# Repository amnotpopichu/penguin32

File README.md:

# penguin32
Penguin32 is a esp32 devboard developed on the esp32 s3fn8 board but with a big penguin on it. why penguin? why not? the main goal here was to develop and learn bare chip work

# Firmware + CAD
N/A, all the necessary programs are preflashed onto the s3 chip. Also no cad for obvious reasons, its just a devboard

# Images
Not sure why some of the models dont actaully render, and some are upside down, so forgive the pcb looking kinda odd.

# Notes
flash not needed thanks to the onboard flash. this is my first time doing bare chip development so im pretty happy with how it turned out given i did it in about 3 days to attempt to qualify for outpost. Honestly i can't believe some of the stuff (routing) took me so long, but i guess i finished at the end of the day so its fine. Also i have two seperate BOMs, a regular BOM, and then a BOM for specific pick and place components. Also i had to use 5 pcba instead of 2, because otherwise it would have made do standard pcba -- which is more expenisve. gsdl doesnt work because jlc doesn't allow it over a certain price.

| Line Item              | Amount (USD) |
|------------------------|--------------|
| MERCHANDISE TOTAL      | 65.78        |
| SHIPPING CHARGE        | 42.78        |
| Customs duties & taxes | 17.78        |
| DISCOUNT               | -15.00       |
| SALES TAX              | 4.90         |
| ORDER TOTAL            | 116.24       |

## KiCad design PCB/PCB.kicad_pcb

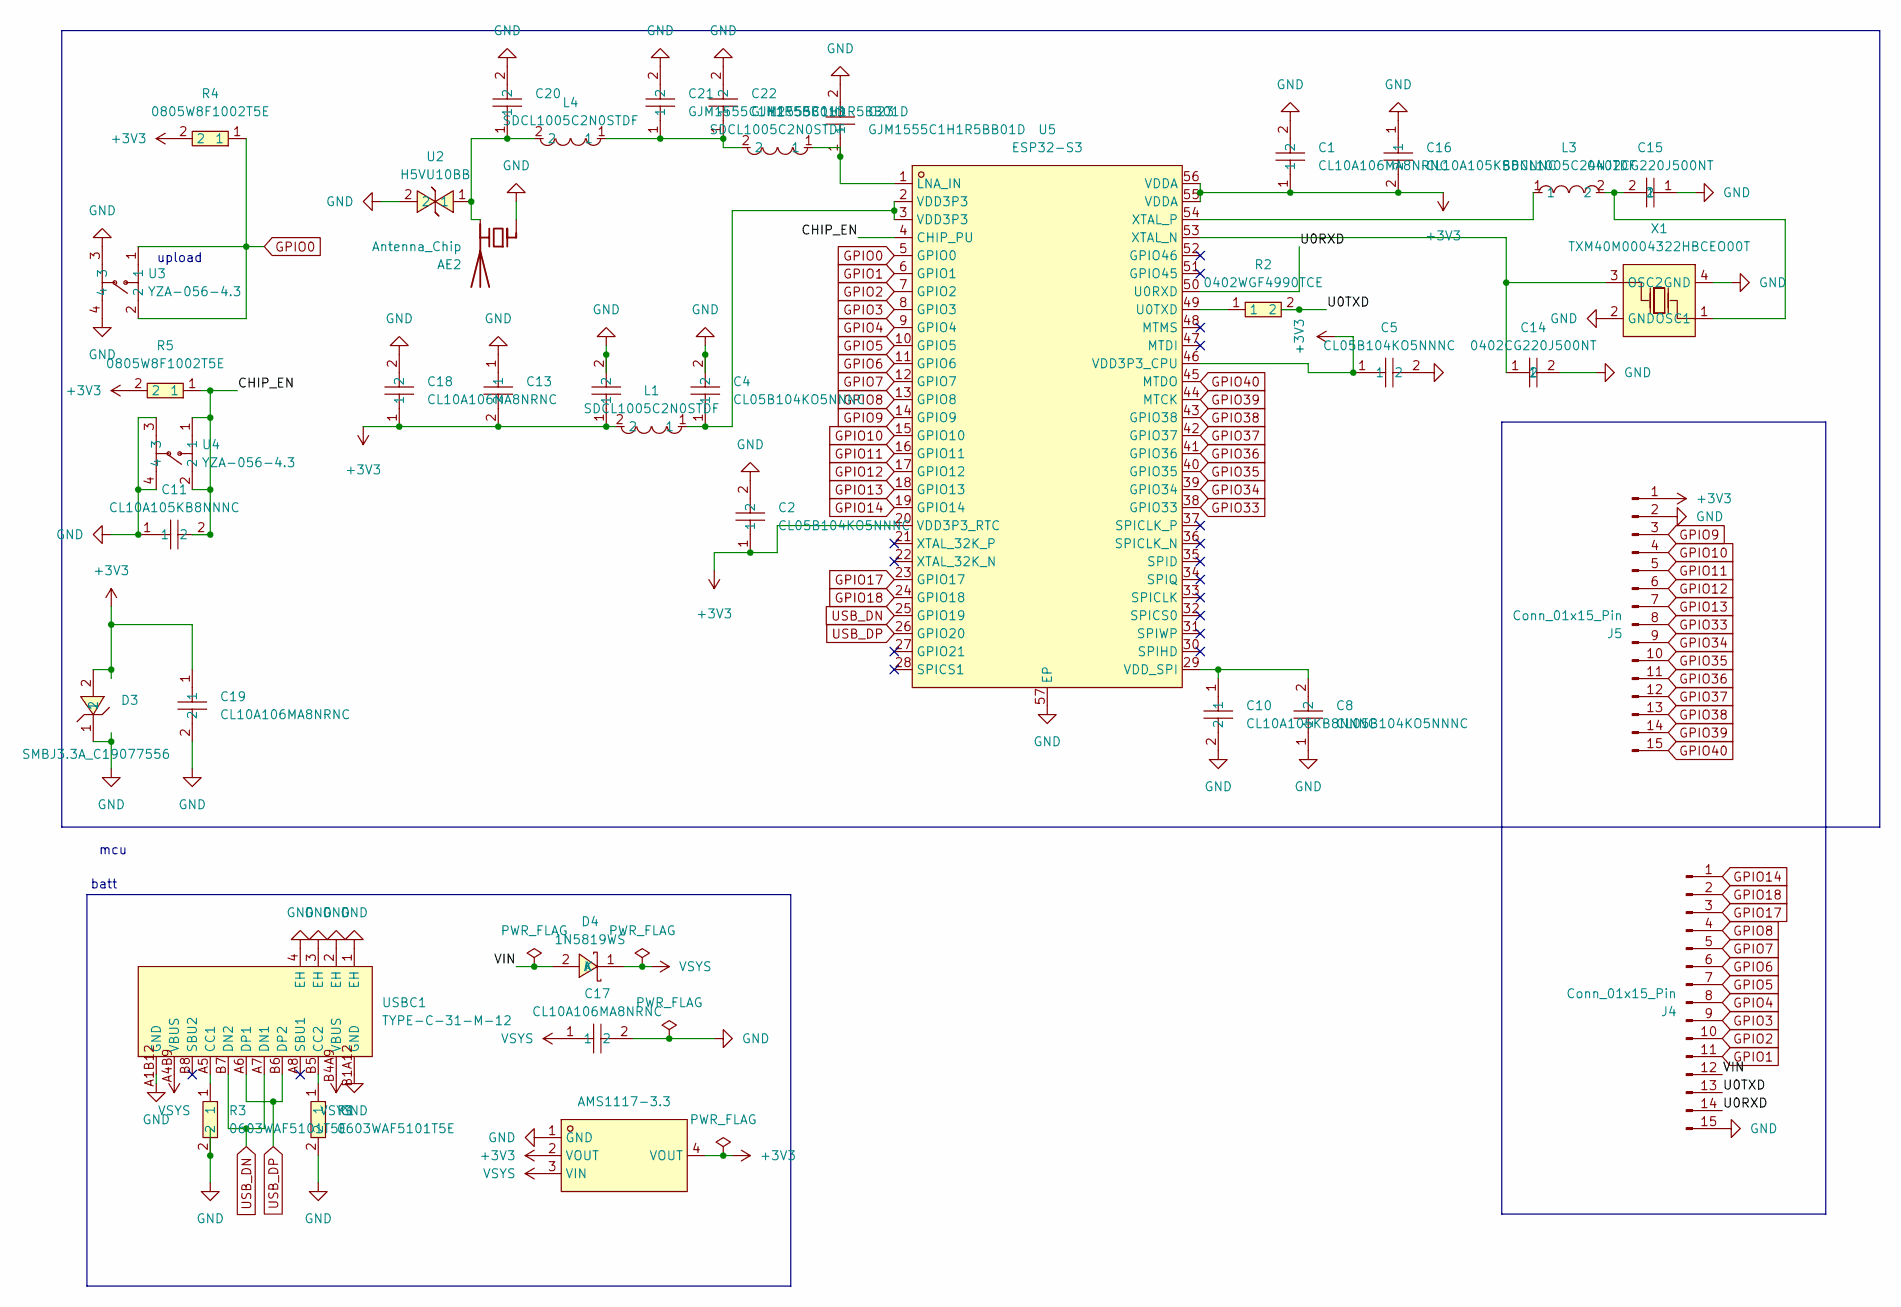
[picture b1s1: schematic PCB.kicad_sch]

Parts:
AE2: Antenna_Chip; ESPRESSIF_ESP32_MIFA_2.4GHz_Right
C1, C17, C18, C19: CL10A106MA8NRNC; C0603; MPN CL10A106MA8NRNC; LCSC Part C96446
C2, C3, C4, C5, C8: CL05B104KO5NNNC; C0402; MPN CL05B104KO5NNNC; LCSC Part C1525
C10, C11, C13, C16: CL10A105KB8NNNC; C0603; MPN CL10A105KB8NNNC; LCSC Part C15849
C14, C15: 0402CG220J500NT; C0402; MPN 0402CG220J500NT; LCSC Part C1555
C20, C21, C22, C23: GJM1555C1H1R5BB01D; C0402; MPN GJM1555C1H1R5BB01D; LCSC Part C76900
D3: SMBJ3.3A_C19077556; SMB_L4.6-W3.6-LS5.3-RD; MPN SMBJ3.3A; LCSC Part C19077556
D4: 1N5819WS; SOD-323_L1.8-W1.3-LS2.5-RD; MPN 1N5819WS; LCSC Part C191023
J4, J5: Conn_01x15_Pin; PinHeader_1x15_P2.54mm_Vertical
L1, L2, L4: SDCL1005C2N0STDF; L0402; MPN SDCL1005C2N0STDF; LCSC Part C43365
L3: SDCL1005C24NJTDF; L0402-RD; MPN SDCL1005C24NJTDF; LCSC Part C74301
R1, R3: 0603WAF5101T5E; R0603; MPN 0603WAF5101T5E; LCSC Part C23186
R2: 0402WGF4990TCE; R0402; MPN 0402WGF4990TCE; LCSC Part C4125
R4, R5: 0805W8F1002T5E; R0805; MPN 0805W8F1002T5E; LCSC Part C17414
U1: AMS1117-3.3; SOT-223-3_L6.5-W3.4-P2.30-LS7.0-BR; MPN AMS1117-3.3; LCSC Part C6186
U2: H5VU10BB; DFN1006-2L-BI; MPN H5VU10BB; LCSC Part C20615786
U3, U4: YZA-056-4.3; SW-SMD_4P-L4.5-W4.5-P3.00-LS6.8; MPN YZA-056-4.3; LCSC Part C49108646
U5: ESP32-S3; QFN-56_L7.0-W7.0-P0.40-TL-EP4.0; MPN ESP32-S3FN8; LCSC Part C2913196
USBC1: TYPE-C-31-M-12; USB-C_SMD-TYPE-C-31-M-12_1; MPN TYPE-C-31-M-12; LCSC Part C165948
X1: TXM40M0004322HBCEO00T; CRYSTAL-SMD_4P-L3.2-W2.5-BL-2; MPN TXM40M0004322HBCEO00T; LCSC Part C284179

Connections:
+3V3: C1.1, C2.1, C3.1, C5.1, C13.2, C16.2, C18.1, C19.1, D3.2, J5.1, L1.2, R4.2, R5.2, U1.2 (VOUT), U1.4 (VOUT), U5.20 (VDD3P3_RTC), U5.46 (VDD3P3_CPU), U5.55 (VDDA), U5.56 (VDDA)
/CHIP_EN: C11.2, R5.1, U4.1, U4.2, U5.4 (CHIP_PU)
/U0RXD: J4.14, U5.50 (U0RXD)
/U0TXD: J4.13, R2.2
/VIN: D4.2 (A), J4.12
GND: AE2.1 (FEED), C1.2, C2.2, C3.2, C4.2, C5.2, C8.1, C10.2, C11.1, C13.1, C14.2, C15.1, C16.1, C17.2, C18.2, C19.2, C20.2, C21.2, C22.2, C23.2, D3.1, J4.15, J5.2, R1.2, R3.2, U1.1 (GND), U2.2, U3.3, U3.4, U4.3, U4.4, U5.57 (EP), USBC1.1 (EH), USBC1.2 (EH), USBC1.3 (EH), USBC1.4 (EH), USBC1.A1B12 (GND), USBC1.B1A12 (GND), X1.2 (GND), X1.4 (GND)
GPIO0: R4.1, U3.1, U3.2, U5.5 (GPIO0)
GPIO1: J4.11, U5.6 (GPIO1)
GPIO2: J4.10, U5.7 (GPIO2)
GPIO3: J4.9, U5.8 (GPIO3)
GPIO4: J4.8, U5.9 (GPIO4)
GPIO5: J4.7, U5.10 (GPIO5)
GPIO6: J4.6, U5.11 (GPIO6)
GPIO7: J4.5, U5.12 (GPIO7)
GPIO8: J4.4, U5.13 (GPIO8)
GPIO9: J5.3, U5.14 (GPIO9)
GPIO10: J5.4, U5.15 (GPIO10)
GPIO11: J5.5, U5.16 (GPIO11)
GPIO12: J5.6, U5.17 (GPIO12)
GPIO13: J5.7, U5.18 (GPIO13)
GPIO14: J4.1, U5.19 (GPIO14)
GPIO17: J4.3, U5.23 (GPIO17)
GPIO18: J4.2, U5.24 (GPIO18)
GPIO33: J5.8, U5.38 (GPIO33)
GPIO34: J5.9, U5.39 (GPIO34)
GPIO35: J5.10, U5.40 (GPIO35)
GPIO36: J5.11, U5.41 (GPIO36)
GPIO37: J5.12, U5.42 (GPIO37)
GPIO38: J5.13, U5.43 (GPIO38)
GPIO39: J5.14, U5.44 (MTCK)
GPIO40: J5.15, U5.45 (MTDO)
unnamed: AE2.2 (PCB_Trace), C20.1, L4.2, U2.1
unnamed: C4.1, L1.1, U5.2 (VDD3P3), U5.3 (VDD3P3)
unnamed: C21.1, C22.1, L2.2, L4.1
unnamed: C23.1, L2.1, U5.1 (LNA_IN)
unnamed: R2.1, U5.49 (U0TXD)
unnamed: C8.2, C10.1, U5.29 (VDD_SPI)
unnamed: C14.1, U5.53 (XTAL_N), X1.3 (OSC2)
unnamed: L3.1, U5.54 (XTAL_P)
unnamed: R3.1, USBC1.A5 (CC1)
unnamed: R1.1, USBC1.B5 (CC2)
unnamed: C15.2, L3.2, X1.1 (OSC1)
USB_DN: U5.25 (GPIO19), USBC1.A7 (DN1), USBC1.B7 (DN2)
USB_DP: U5.26 (GPIO20), USBC1.A6 (DP1), USBC1.B6 (DP2)
VSYS: C17.1, D4.1 (K), U1.3 (VIN), USBC1.A4B9 (VBUS), USBC1.B4A9 (VBUS)

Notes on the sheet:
batt
upload
mcu

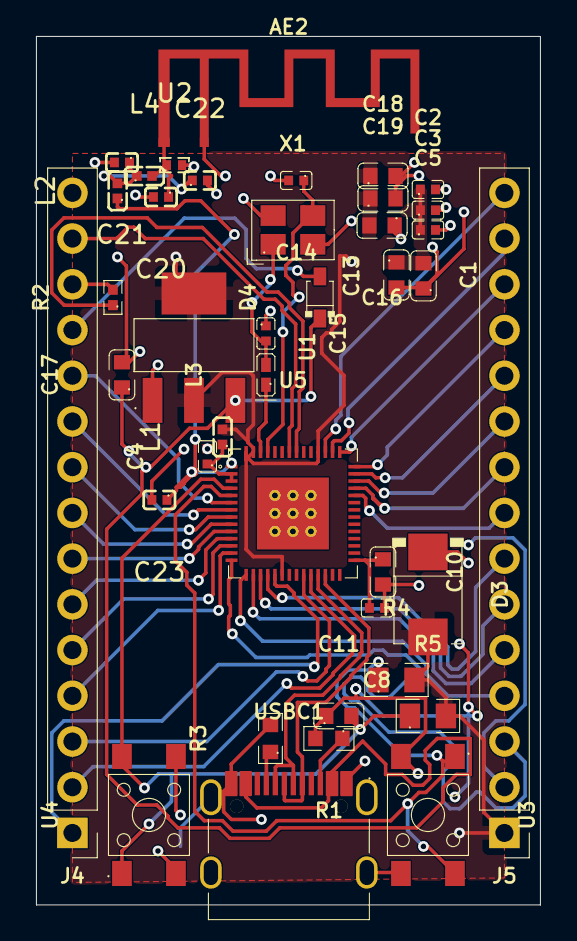
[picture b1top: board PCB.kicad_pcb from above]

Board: 2 copper layers, 28.0 x 48.2 mm, 40 parts (0 on the bottom side), 45 nets.
